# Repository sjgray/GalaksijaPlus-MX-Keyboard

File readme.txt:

Galaksija Plus MX Keyboard   (C)2024 Steve J. Gray
==========================   www.sjgray.ca

"GAL-V1-R1"

This is an MX keyboard for the Galaksija Plus computer.
It uses a 6.25u spacebar and is close to, but modified
compared to the standard layout in order to use modern
PC-type MX keycaps.

Included are the Kicad 7 design files.
Gerbers are included that can be sent to the board
house.

Steve

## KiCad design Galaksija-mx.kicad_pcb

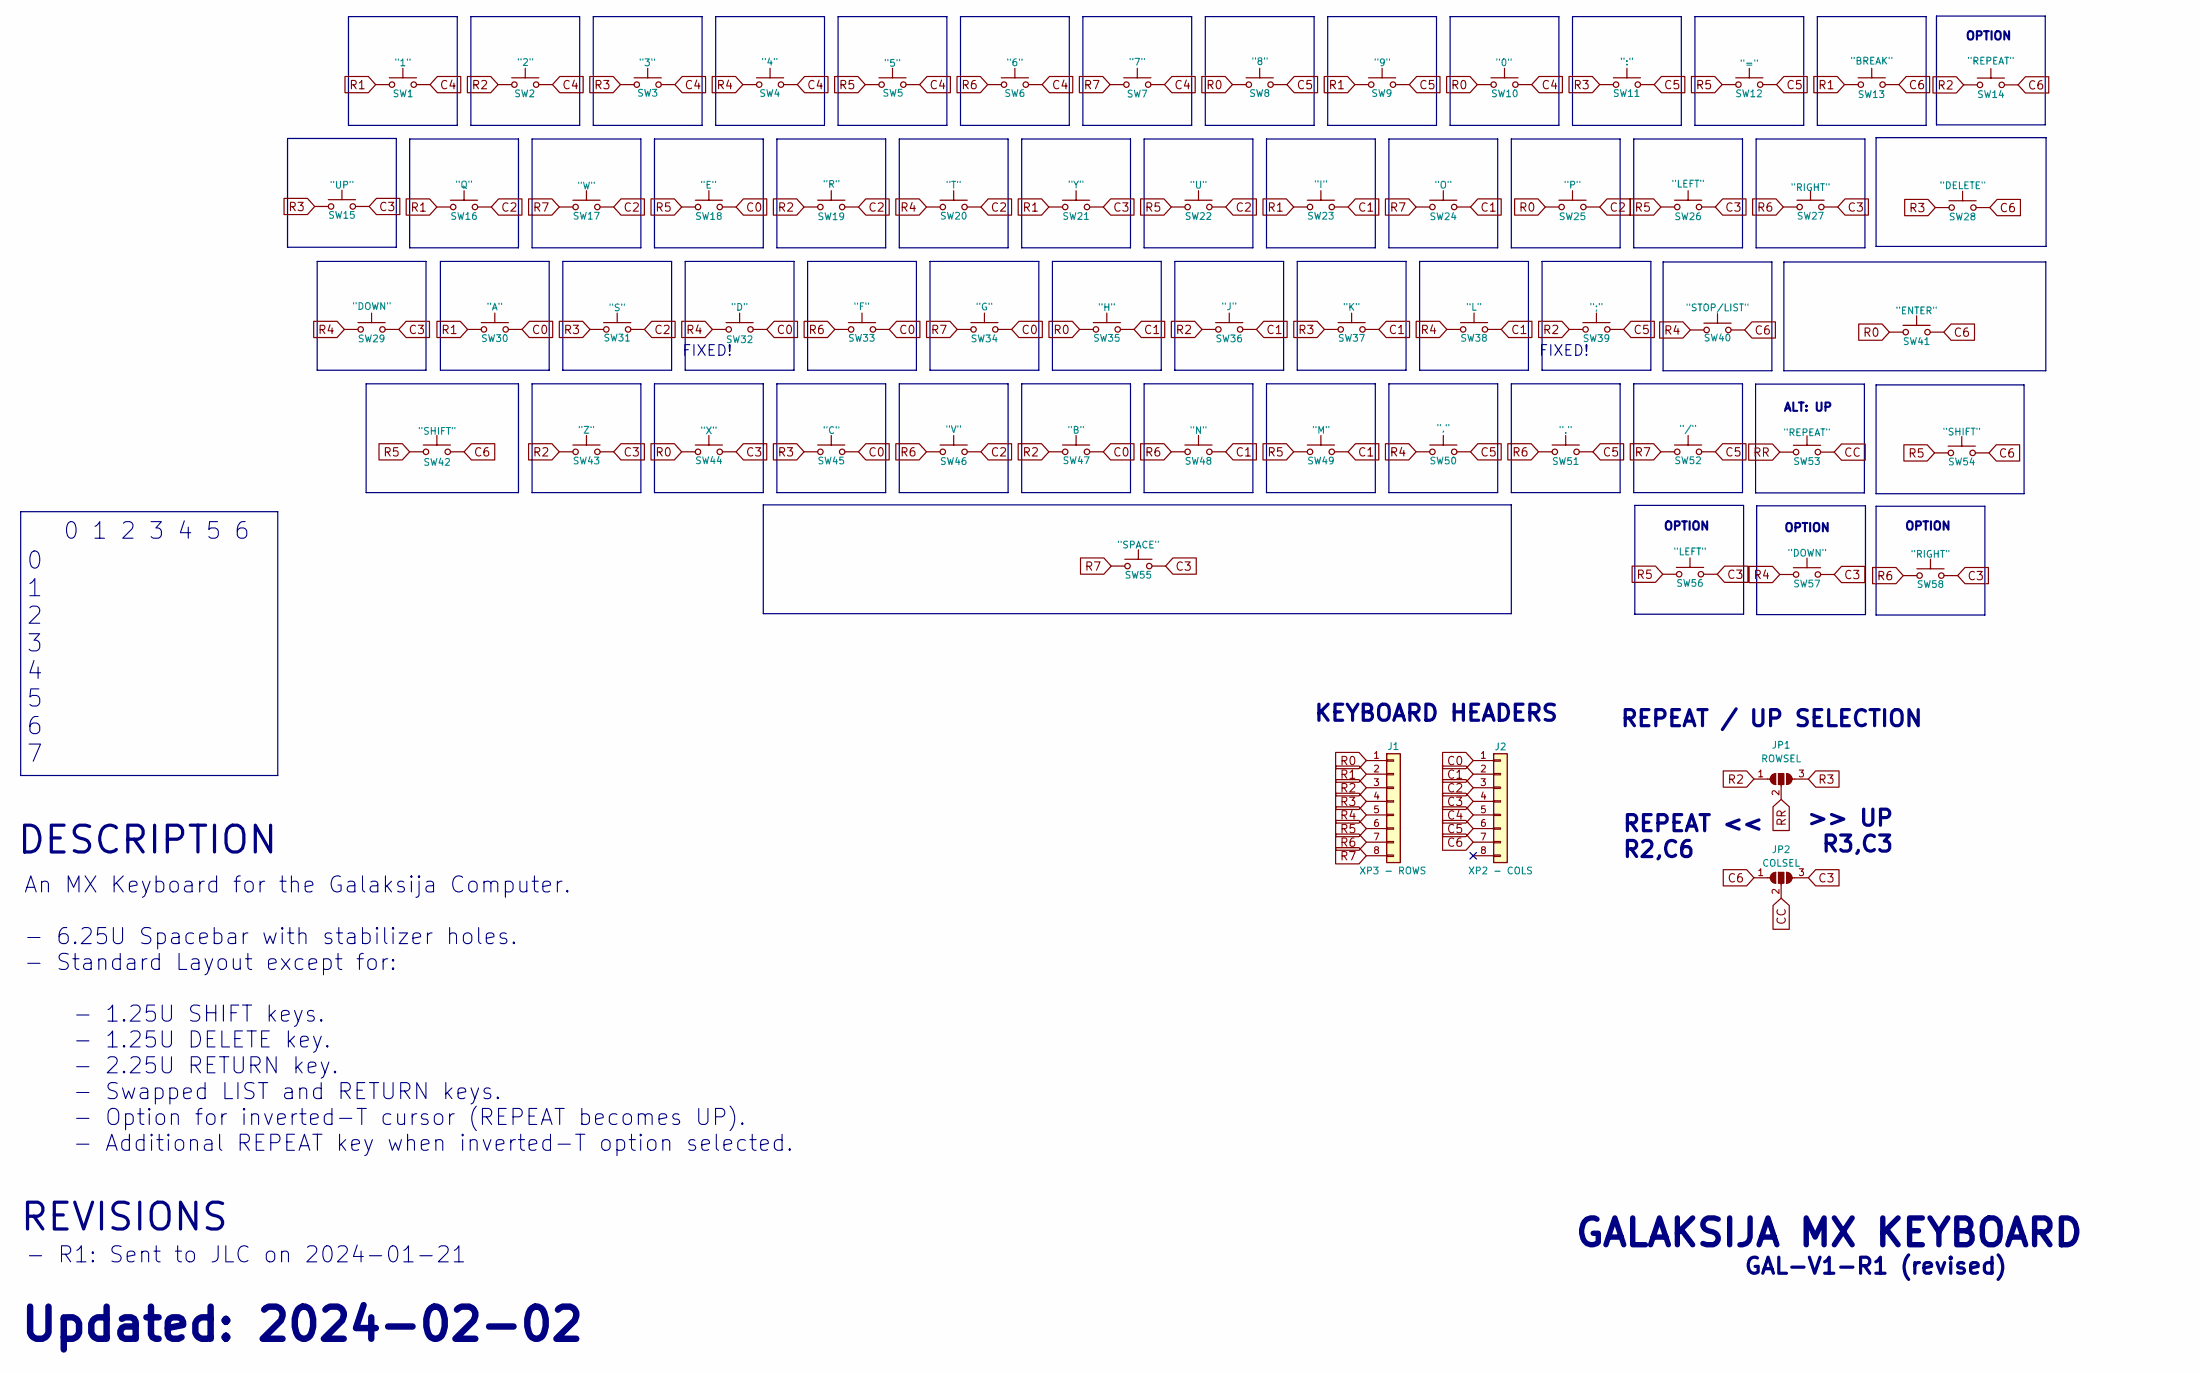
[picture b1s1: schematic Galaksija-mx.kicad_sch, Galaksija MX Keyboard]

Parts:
J1: XP3 - ROWS; PinHeader_1x08_P2.54mm_Vertical
J2: XP2 - COLS; PinHeader_1x08_P2.54mm_Vertical
JP1: ROWSEL; SolderJumper-3_P1.3mm_Open_RoundedPad1.0x1.5mm_NumberLabels
JP2: COLSEL; SolderJumper-3_P1.3mm_Open_RoundedPad1.0x1.5mm_NumberLabels
SW1: "1"; SW_Hybrid_CherryMX_GateronLP_1.00u_PCB
SW2: "2"; SW_Hybrid_CherryMX_GateronLP_1.00u_PCB
SW3: "3"; SW_Hybrid_CherryMX_GateronLP_1.00u_PCB
SW4: "4"; SW_Hybrid_CherryMX_GateronLP_1.00u_PCB
SW5: "5"; SW_Hybrid_CherryMX_GateronLP_1.00u_PCB
SW6: "6"; SW_Hybrid_CherryMX_GateronLP_1.00u_PCB
SW7: "7"; SW_Hybrid_CherryMX_GateronLP_1.00u_PCB
SW8: "8"; SW_Hybrid_CherryMX_GateronLP_1.00u_PCB
SW9: "9"; SW_Hybrid_CherryMX_GateronLP_1.00u_PCB
SW10: "0"; SW_Hybrid_CherryMX_GateronLP_1.00u_PCB
SW11: ":"; SW_Hybrid_CherryMX_GateronLP_1.00u_PCB
SW12: "="; SW_Hybrid_CherryMX_GateronLP_1.00u_PCB
SW13: "BREAK"; SW_Hybrid_CherryMX_GateronLP_1.00u_PCB
SW14, SW53: "REPEAT"; SW_Hybrid_CherryMX_GateronLP_1.00u_PCB
SW15: "UP"; SW_Hybrid_CherryMX_GateronLP_1.00u_PCB
SW16: "Q"; SW_Hybrid_CherryMX_GateronLP_1.00u_PCB
SW17: "W"; SW_Hybrid_CherryMX_GateronLP_1.00u_PCB
SW18: "E"; SW_Hybrid_CherryMX_GateronLP_1.00u_PCB
SW19: "R"; SW_Hybrid_CherryMX_GateronLP_1.00u_PCB
SW20: "T"; SW_Hybrid_CherryMX_GateronLP_1.00u_PCB
SW21: "Y"; SW_Hybrid_CherryMX_GateronLP_1.00u_PCB
SW22: "U"; SW_Hybrid_CherryMX_GateronLP_1.00u_PCB
SW23: "I"; SW_Hybrid_CherryMX_GateronLP_1.00u_PCB
SW24: "O"; SW_Hybrid_CherryMX_GateronLP_1.00u_PCB
SW25: "P"; SW_Hybrid_CherryMX_GateronLP_1.00u_PCB
SW26, SW56: "LEFT"; SW_Hybrid_CherryMX_GateronLP_1.00u_PCB
SW27, SW58: "RIGHT"; SW_Hybrid_CherryMX_GateronLP_1.00u_PCB
SW28: "DELETE"; SW_Hybrid_CherryMX_GateronLP_1.50u_PCB
SW29, SW57: "DOWN"; SW_Hybrid_CherryMX_GateronLP_1.00u_PCB
SW30: "A"; SW_Hybrid_CherryMX_GateronLP_1.00u_PCB
SW31: "S"; SW_Hybrid_CherryMX_GateronLP_1.00u_PCB
SW32: "D"; SW_Hybrid_CherryMX_GateronLP_1.00u_PCB
SW33: "F"; SW_Hybrid_CherryMX_GateronLP_1.00u_PCB
SW34: "G"; SW_Hybrid_CherryMX_GateronLP_1.00u_PCB
SW35: "H"; SW_Hybrid_CherryMX_GateronLP_1.00u_PCB
SW36: "J"; SW_Hybrid_CherryMX_GateronLP_1.00u_PCB
SW37: "K"; SW_Hybrid_CherryMX_GateronLP_1.00u_PCB
SW38: "L"; SW_Hybrid_CherryMX_GateronLP_1.00u_PCB
SW39: ";"; SW_Hybrid_CherryMX_GateronLP_1.00u_PCB
SW40: "STOP/LIST"; SW_Hybrid_CherryMX_GateronLP_1.00u_PCB
SW41: "ENTER"; SW_Hybrid_CherryMX_GateronLP_2.25u_PCB
SW42, SW54: "SHIFT"; SW_Hybrid_CherryMX_GateronLP_1.25u_PCB
SW43: "Z"; SW_Hybrid_CherryMX_GateronLP_1.00u_PCB
SW44: "X"; SW_Hybrid_CherryMX_GateronLP_1.00u_PCB
SW45: "C"; SW_Hybrid_CherryMX_GateronLP_1.00u_PCB
SW46: "V"; SW_Hybrid_CherryMX_GateronLP_1.00u_PCB
SW47: "B"; SW_Hybrid_CherryMX_GateronLP_1.00u_PCB
SW48: "N"; SW_Hybrid_CherryMX_GateronLP_1.00u_PCB
SW49: "M"; SW_Hybrid_CherryMX_GateronLP_1.00u_PCB
SW50: ","; SW_Hybrid_CherryMX_GateronLP_1.00u_PCB
SW51: "."; SW_Hybrid_CherryMX_GateronLP_1.00u_PCB
SW52: "/"; SW_Hybrid_CherryMX_GateronLP_1.00u_PCB
SW55: "SPACE"; SW_Hybrid_CherryMX_GateronLP_6.25u_PCB

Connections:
C0: J2.1, SW18.2, SW30.2, SW32.2, SW33.2, SW34.2, SW45.2, SW47.2
C1: J2.2, SW23.2, SW24.2, SW35.2, SW36.2, SW37.2, SW38.2, SW48.2, SW49.2
C2: J2.3, SW16.2, SW17.2, SW19.2, SW20.2, SW22.2, SW25.2, SW31.2, SW46.2
C3: J2.4, JP2.3 (B), SW15.2, SW21.2, SW26.2, SW27.2, SW29.2, SW43.2, SW44.2, SW55.2, SW56.2, SW57.2, SW58.2
C4: J2.5, SW1.2, SW2.2, SW3.2, SW4.2, SW5.2, SW6.2, SW7.2, SW10.2
C5: J2.6, SW8.2, SW9.2, SW11.2, SW12.2, SW39.2, SW50.2, SW51.2, SW52.2
C6: J2.7, JP2.1 (A), SW13.2, SW14.2, SW28.2, SW40.2, SW41.2, SW42.2, SW54.2
CC: JP2.2 (C), SW53.2
R0: J1.1, SW8.1, SW10.1, SW25.1, SW35.1, SW41.1, SW44.1
R1: J1.2, SW1.1, SW9.1, SW13.1, SW16.1, SW21.1, SW23.1, SW30.1
R2: J1.3, JP1.1 (A), SW2.1, SW14.1, SW19.1, SW36.1, SW39.1, SW43.1, SW47.1
R3: J1.4, JP1.3 (B), SW3.1, SW11.1, SW15.1, SW28.1, SW31.1, SW37.1, SW45.1
R4: J1.5, SW4.1, SW20.1, SW29.1, SW32.1, SW38.1, SW40.1, SW50.1, SW57.1
R5: J1.6, SW5.1, SW12.1, SW18.1, SW22.1, SW26.1, SW42.1, SW49.1, SW54.1, SW56.1
R6: J1.7, SW6.1, SW27.1, SW33.1, SW46.1, SW48.1, SW51.1, SW58.1
R7: J1.8, SW7.1, SW17.1, SW24.1, SW34.1, SW52.1, SW55.1
RR: JP1.2 (C), SW53.1

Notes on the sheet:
0 1 2 3 4 5 6
OPTION
0 1 2 3 4 5 6 7
FIXED!
DESCRIPTION
An MX Keyboard for the Galaksija Computer. - 6.25U Spacebar with stabilizer holes. - Standard Layout except for: - 1.25U SHIFT keys. - 1.25U DELETE key. - 2.25U RETURN key. - Swapped LIST and RETURN keys. - Option for inverted-T cursor (REPEAT becomes UP). - Additional REPEAT key when inverted-T op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
GAL-V1-R1 (revised)
REPEAT / UP SELECTION
KEYBOARD HEADERS
GALAKSIJA MX KEYBOARD
>> UP R3,C3
REVISIONS
REPEAT << R2,C6
Updated: 2024-02-02
- R1: Sent to JLC on 2024-01-21
ALT: UP

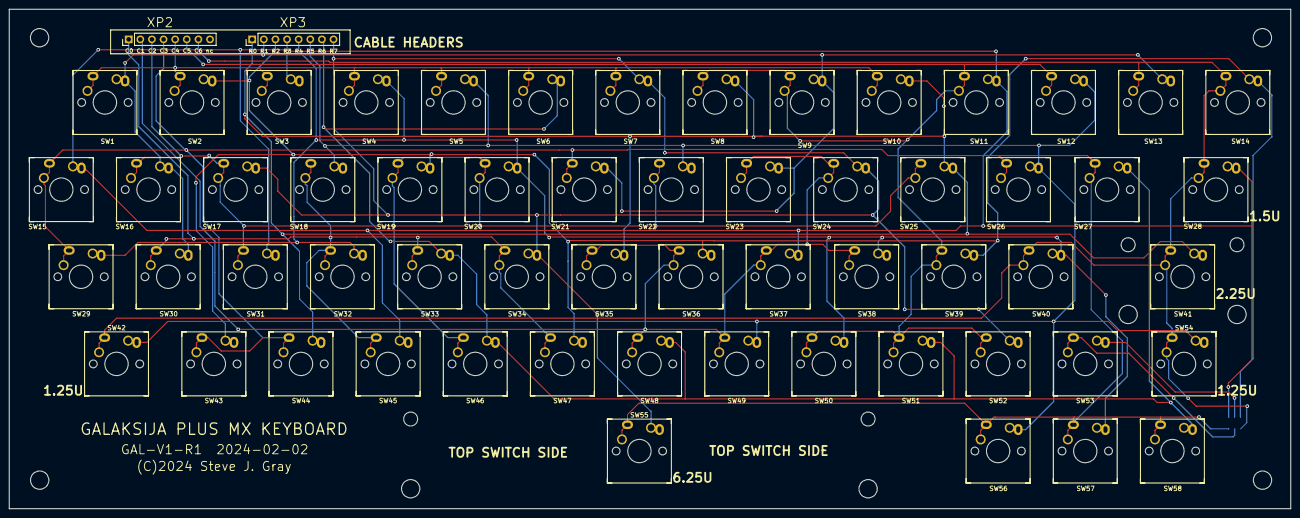
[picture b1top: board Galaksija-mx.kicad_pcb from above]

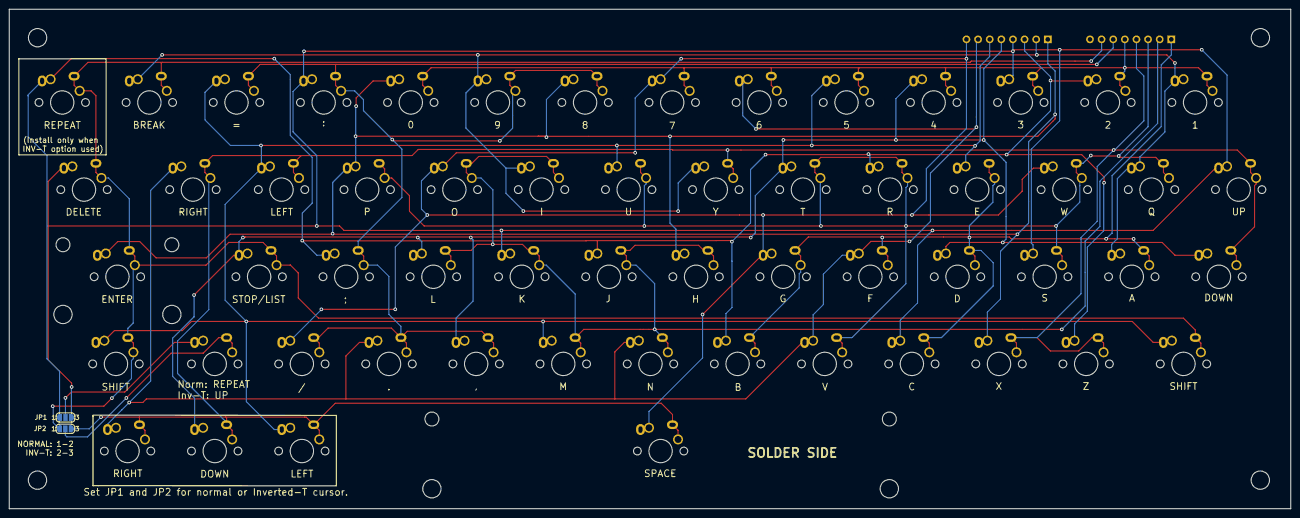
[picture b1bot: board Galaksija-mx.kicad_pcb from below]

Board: 2 copper layers, 280.1 x 109.2 mm, 62 parts (2 on the bottom side), 17 nets.

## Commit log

2024-02-02 GAL-V1-R1 Initial Release
    Initial release. The first prototype PCB had a few minor errors but was mostly funtional. This release fixes those errors and is slightly updated.
